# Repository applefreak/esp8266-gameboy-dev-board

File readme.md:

# ESP8266 Gameboy Dev Board

Your go to dev board for Gameboy accessories development, powered by ESP8266.

For details, check out the [blog post here](https://poyu.xyz/projects/esp8266-gameboy-dev-board/)!

## License

MIT: https://poyu.mit-license.org/

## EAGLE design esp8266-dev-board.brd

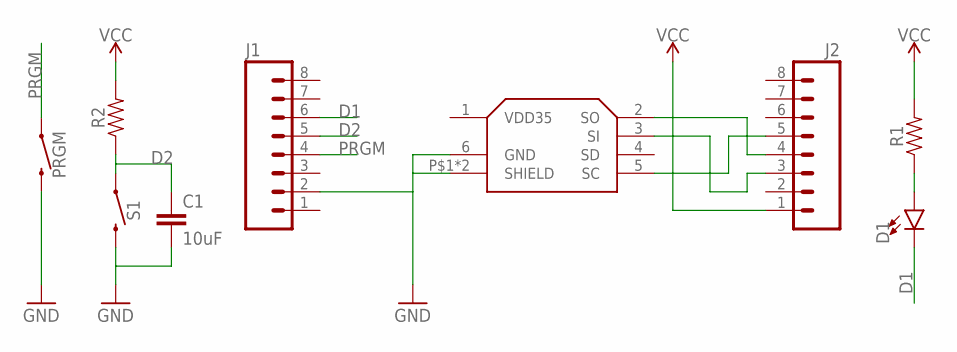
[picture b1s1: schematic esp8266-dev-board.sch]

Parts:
C1: 10uF; 0805
D1: LED0603; LED-0603
J1, J2: M08; 1X08_ROUND
PRGM: MOMENTARY-SWITCH-SPST-SMD-6.0X3.5MM; TACTILE_SWITCH_SMD_6.0X3.5MM
R1, R2: 0805
S1: MOMENTARY-SWITCH-SPST-SMD-6.0X3.5MM; TACTILE_SWITCH_SMD_6.0X3.5MM
U$1: EXT-PORT-AGB

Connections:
D1: D1.C, J1.6
D2: C1.1, J1.5, R2.1, S1.1
GND: C1.2, J1.2, PRGM.2, S1.2, U$1.6 (GND), U$1.P$1 (SHIELD), U$1.P$2 (SHIELD)
unnamed: J2.5, U$1.5 (SC)
unnamed: J2.4, U$1.2 (SO)
unnamed: J2.3, U$1.3 (SI)
unnamed: D1.A, R1.1
PRGM: J1.4, PRGM.1
VCC: J2.1, R1.2, R2.2

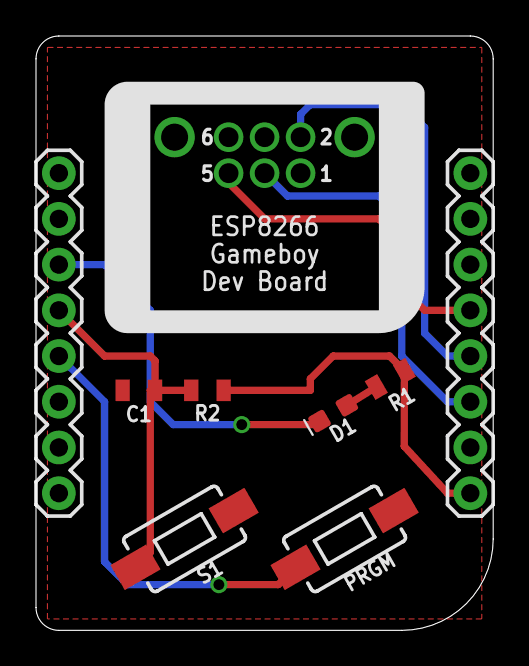
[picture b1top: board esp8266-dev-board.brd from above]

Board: 2 copper layers, 25.4 x 33.0 mm, 9 parts (1 on the bottom side), 9 nets.

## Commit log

2017-03-29 [init] board updated
2020-10-14 added license file

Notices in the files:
parts and their libraries:
SparkFun-Capacitors: Licensing: Creative Commons ShareAlike 4.0 International - https://creativecommons.org/licenses/by-sa/4.0
